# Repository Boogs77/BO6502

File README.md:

**SPECIFICATION**

MICROPROCESSOR The Western Design Center Inc. W65C02S

Clock frequency 1.0 MHz

Optional Clock frequency 2.0 MHz e 500 KHz

ROM Memory ATMEL AT28C256

On-board ROM capacitor 32 Kbyte

RAM Memory HITACHI HM62256lp-12

On-board RAM capacitor 32 Kbyte

VIDEO OUTPUT LCD Display 16x2

Internal Chip HITACHI HD44780U

SERIAL COMMUNICATION Through serial port DB9

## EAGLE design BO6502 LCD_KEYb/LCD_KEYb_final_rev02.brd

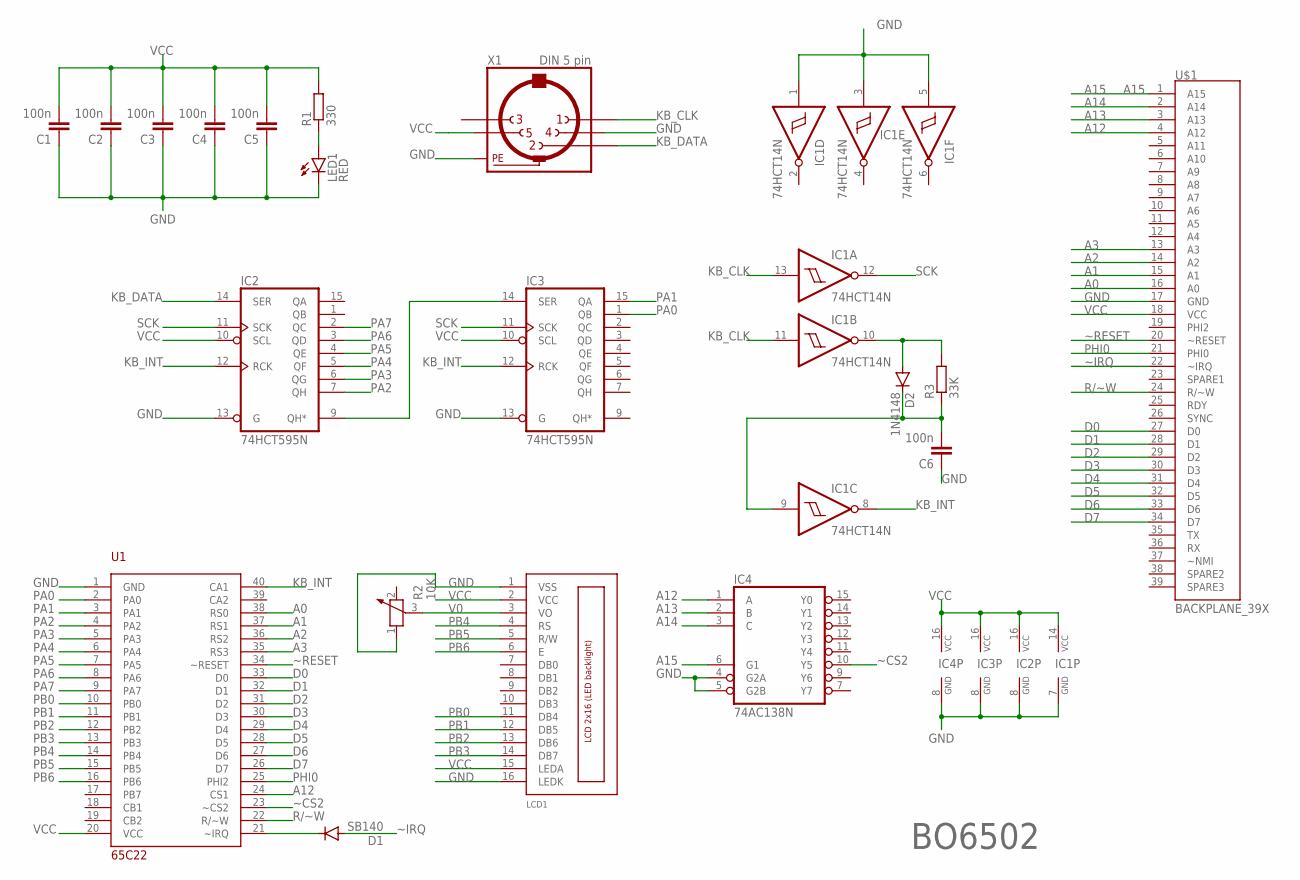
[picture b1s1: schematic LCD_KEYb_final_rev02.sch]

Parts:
C1, C2, C3, C4, C5, C6: 100n; C025-025X050
D1: SB140; DO41-10
D2: 1N4148; DO35-7
IC1: 74HCT14N; DIL14
IC2, IC3: 74HCT595N; DIL16
IC4: 74AC138N; DIL16
LCD1: LCD_2X16_SIL; HY-1602F
LED1: RED; LED5MM
R1: 330; 0207/10
R2: 10K; PT-10
R3: 33K; 0207/10
U1: 65C22; DIL40
U$1: BACKPLANE_39X; BP_39X
X1: DIN 5 pin; MAB5SH

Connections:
A0: U1.38 (RS0), U$1.16 (A0)
A1: U1.37 (RS1), U$1.15 (A1)
A2: U1.36 (RS2), U$1.14 (A2)
A3: U1.35 (RS3), U$1.13 (A3)
A12: IC4.1 (A), U1.24 (CS1), U$1.4 (A12)
A13: IC4.2 (B), U$1.3 (A13)
A14: IC4.3 (C), U$1.2 (A14)
A15: IC4.6 (G1), U$1.1 (A15)
D0: U1.33 (D0), U$1.27 (D0)
D1: U1.32 (D1), U$1.28 (D1)
D2: U1.31 (D2), U$1.29 (D2)
D3: U1.30 (D3), U$1.30 (D3)
D4: U1.29 (D4), U$1.31 (D4)
D5: U1.28 (D5), U$1.32 (D5)
D6: U1.27 (D6), U$1.33 (D6)
D7: U1.26 (D7), U$1.34 (D7)
GND: C1.1, C2.1, C3.1, C4.1, C5.1, C6.1, IC1.1 (I), IC1.3 (I), IC1.5 (I), IC1.7 (GND), IC2.8 (GND), IC2.13 (G), IC3.8 (GND), IC3.13 (G), IC4.4 (G2A), IC4.5 (G2B), IC4.8 (GND), LCD1.1 (VSS), LCD1.16 (LEDK), LED1.K (C), R2.1, U1.1 (GND), U$1.17 (GND), X1.4, X1.PE, X1.PE@ (PE)
KB_CLK: IC1.11 (I), IC1.13 (I), X1.1
KB_DATA: IC2.14 (SER), X1.2
KB_INT: IC1.8 (O), IC2.12 (RCK), IC3.12 (RCK), U1.40 (CA1)
unnamed: D1.C, U1.21 (~IRQ)
unnamed: IC2.9 (QH*), IC3.14 (SER)
unnamed: D2.A, IC1.10 (O), R3.2
unnamed: C6.2, D2.C, IC1.9 (I), R3.1
unnamed: LED1.A, R1.1
PA0: IC3.1 (QB), U1.2 (PA0)
PA1: IC3.15 (QA), U1.3 (PA1)
PA2: IC2.7 (QH), U1.4 (PA2)
PA3: IC2.6 (QG), U1.5 (PA3)
PA4: IC2.5 (QF), U1.6 (PA4)
PA5: IC2.4 (QE), U1.7 (PA5)
PA6: IC2.3 (QD), U1.8 (PA6)
PA7: IC2.2 (QC), U1.9 (PA7)
PB0: LCD1.11 (DB4), U1.10 (PB0)
PB1: LCD1.12 (DB5), U1.11 (PB1)
PB2: LCD1.13 (DB6), U1.12 (PB2)
PB3: LCD1.14 (DB7), U1.13 (PB3)
PB4: LCD1.4 (RS), U1.14 (PB4)
PB5: LCD1.5 (R/W), U1.15 (PB5)
PB6: LCD1.6 (E), U1.16 (PB6)
PHI0: U1.25 (PHI2), U$1.21 (PHI0)
R/~W: U1.22 (R/~W), U$1.24 (R/~W)
SCK: IC1.12 (O), IC2.11 (SCK), IC3.11 (SCK)
V0: LCD1.3 (VO), R2.3
VCC: C1.2, C2.2, C3.2, C4.2, C5.2, IC1.14 (VCC), IC2.10 (SCL), IC2.16 (VCC), IC3.10 (SCL), IC3.16 (VCC), IC4.16 (VCC), LCD1.2 (VCC), LCD1.15 (LEDA), R1.2, U1.20 (VCC), U$1.18 (VCC), X1.5
~CS2: IC4.10 (Y5), U1.23 (~CS2)
~IRQ: D1.A, U$1.22 (~IRQ)
~RESET: U1.34 (~RESET), U$1.20 (~RESET)

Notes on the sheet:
BO6502

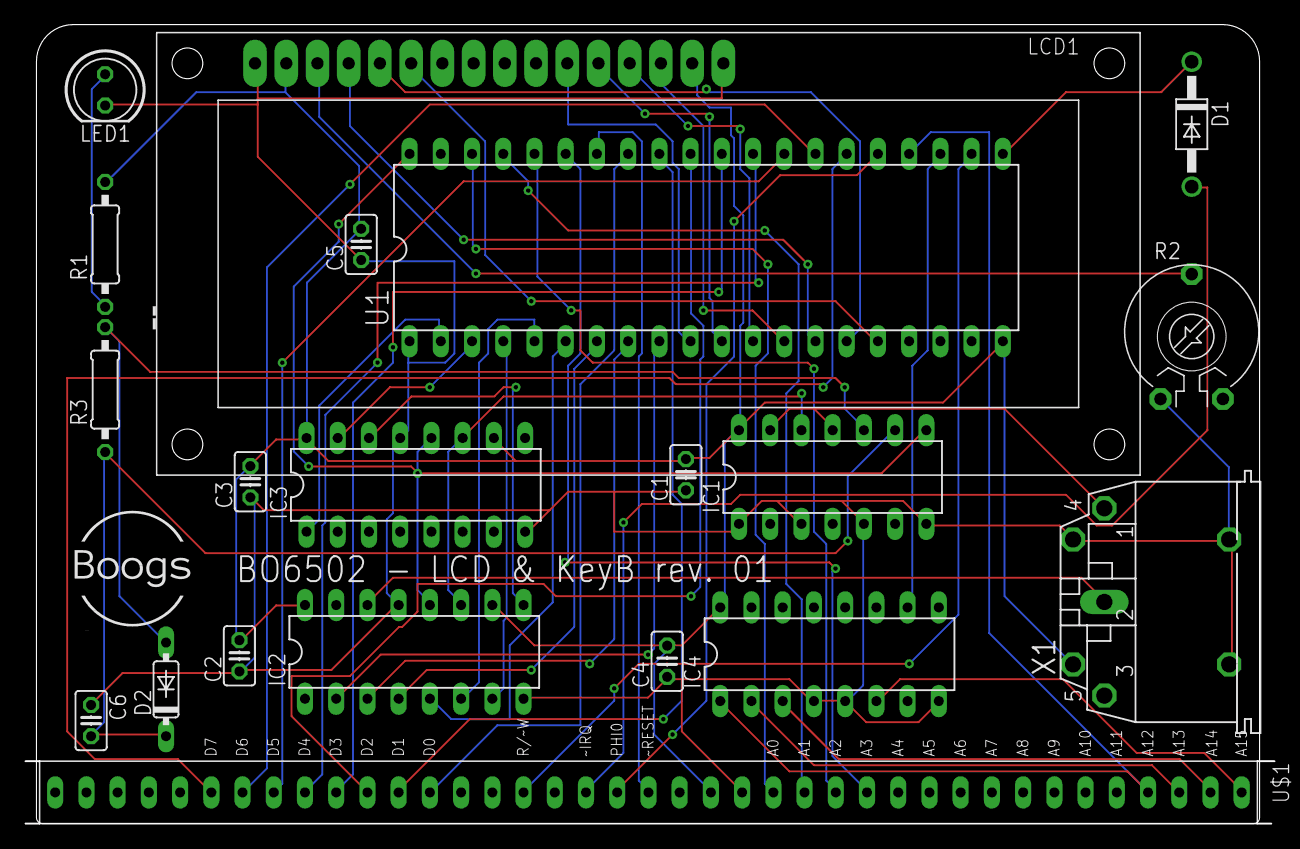
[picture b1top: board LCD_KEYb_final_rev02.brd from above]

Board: 2 copper layers, 101.6 x 64.9 mm, 20 parts (0 on the bottom side), 48 nets.

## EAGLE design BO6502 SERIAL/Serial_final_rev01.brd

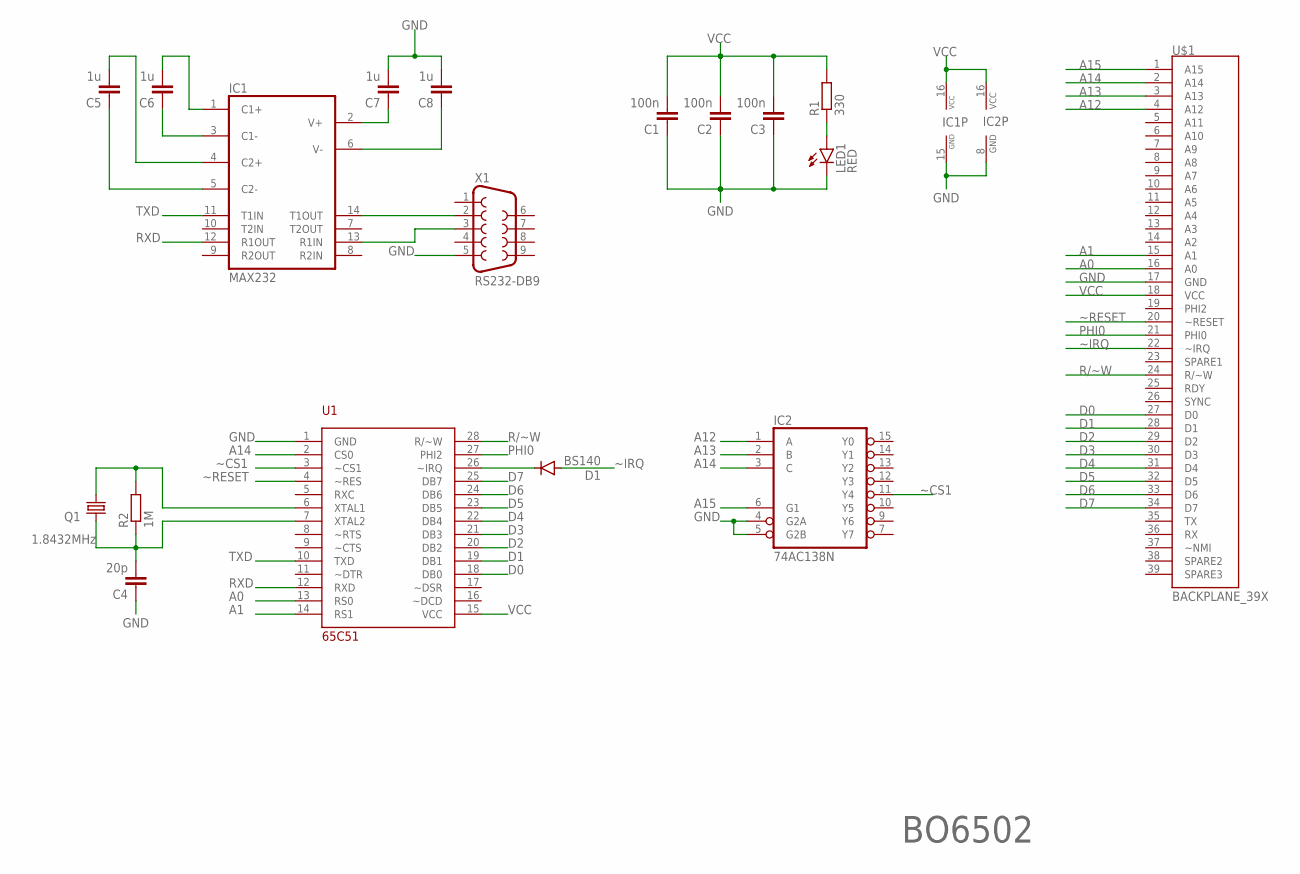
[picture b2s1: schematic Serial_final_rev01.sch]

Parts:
C1, C2, C3: 100n; C025-025X050
C4: 20p; C025-025X050
C5, C6, C7, C8: 1u; C050-025X075
D1: BS140; DO41-10
IC1: MAX232; DIL16
IC2: 74AC138N; DIL16
LED1: RED; LED5MM
Q1: 1.8432MHz; HC49/S
R1: 330; 0207/10
R2: 1M; 0207/10
U1: 65C51; DIL28
U$1: BACKPLANE_39X; BP_39X
X1: RS232-DB9; F09HP

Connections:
A0: U1.13 (RS0), U$1.16 (A0)
A1: U1.14 (RS1), U$1.15 (A1)
A12: IC2.1 (A), U$1.4 (A12)
A13: IC2.2 (B), U$1.3 (A13)
A14: IC2.3 (C), U1.2 (CS0), U$1.2 (A14)
A15: IC2.6 (G1), U$1.1 (A15)
D0: U1.18 (DB0), U$1.27 (D0)
D1: U1.19 (DB1), U$1.28 (D1)
D2: U1.20 (DB2), U$1.29 (D2)
D3: U1.21 (DB3), U$1.30 (D3)
D4: U1.22 (DB4), U$1.31 (D4)
D5: U1.23 (DB5), U$1.32 (D5)
D6: U1.24 (DB6), U$1.33 (D6)
D7: U1.25 (DB7), U$1.34 (D7)
GND: C1.1, C2.1, C3.1, C4.1, C7.2, C8.2, IC1.15 (GND), IC2.4 (G2A), IC2.5 (G2B), IC2.8 (GND), LED1.K (C), U1.1 (GND), U$1.17 (GND), X1.5
unnamed: C6.2, IC1.1 (C1+)
unnamed: D1.C, U1.26 (~IRQ)
unnamed: C6.1, IC1.3 (C1-)
unnamed: C5.2, IC1.4 (C2+)
unnamed: C5.1, IC1.5 (C2-)
unnamed: LED1.A, R1.1
unnamed: IC1.14 (T1OUT), X1.2
unnamed: IC1.13 (R1IN), X1.3
unnamed: C7.1, IC1.2 (V+)
unnamed: C8.1, IC1.6 (V-)
unnamed: Q1.2, R2.2, U1.6 (XTAL1)
unnamed: C4.2, Q1.1, R2.1, U1.7 (XTAL2)
PHI0: U1.27 (PHI2), U$1.21 (PHI0)
R/~W: U1.28 (R/~W), U$1.24 (R/~W)
RXD: IC1.12 (R1OUT), U1.12 (RXD)
TXD: IC1.11 (T1IN), U1.10 (TXD)
VCC: C1.2, C2.2, C3.2, IC1.16 (VCC), IC2.16 (VCC), R1.2, U1.15 (VCC), U$1.18 (VCC)
~CS1: IC2.11 (Y4), U1.3 (~CS1)
~IRQ: D1.A, U$1.22 (~IRQ)
~RESET: U1.4 (~RES), U$1.20 (~RESET)

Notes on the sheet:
BO6502

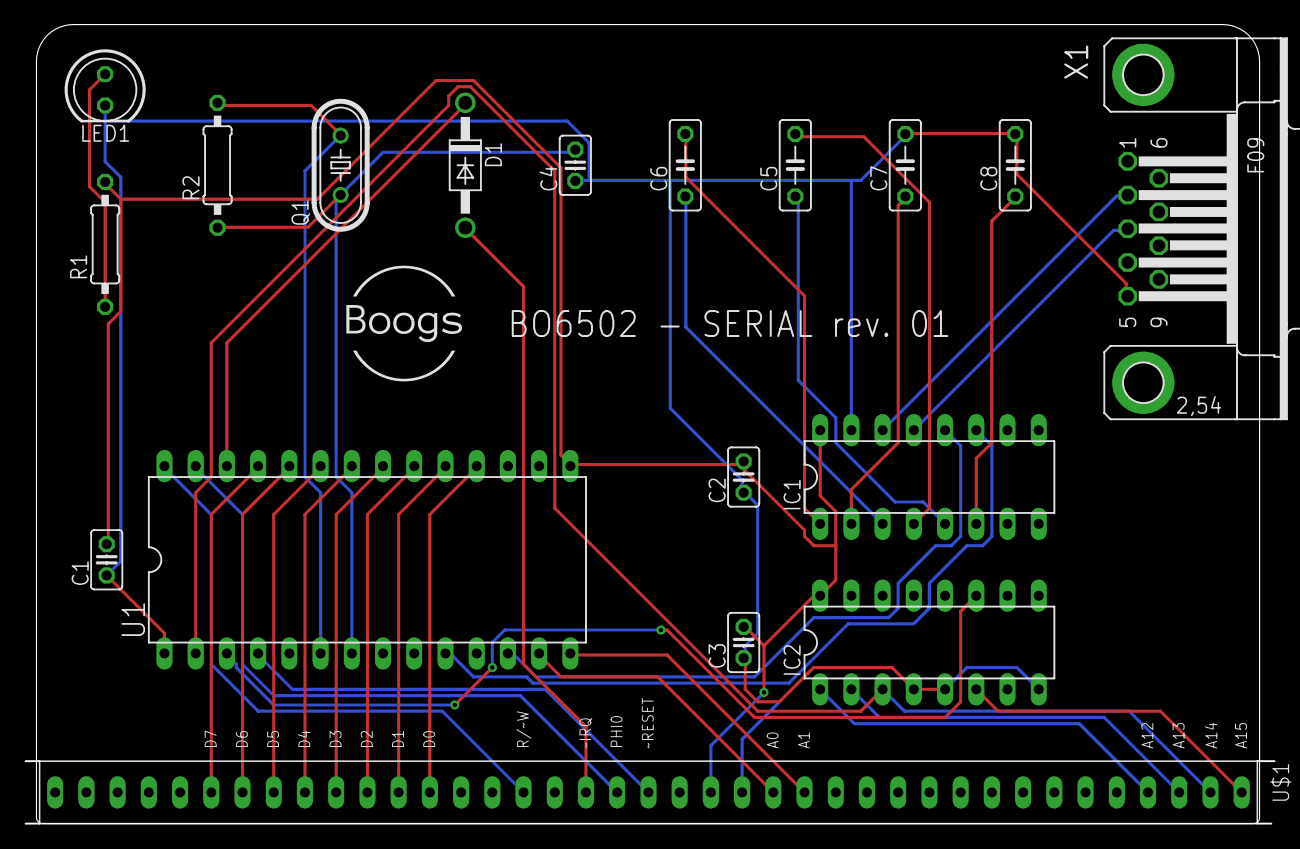
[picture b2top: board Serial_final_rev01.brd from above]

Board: 2 copper layers, 101.6 x 64.9 mm, 18 parts (0 on the bottom side), 35 nets.

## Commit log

2024-10-03 Create BO6502 ROM
2024-10-04 Rename CPU_001_2024-02-26.zip to BO6502_CPU.zip
2024-10-04 Rename BO6502_CPU.zip to BO6502_CPU_gerber.zip
2024-10-04 Rename ROM_001_2024-03-04.zip to BO6502_ROM_gerber.zip
2024-10-04 Adding RAM
2024-10-04 adding
2024-10-04 adding PDF sch
2024-10-05 R3 wrong value
2025-06-01 Create BO6502-LCDBIG.pdf
    add BIGLCD
